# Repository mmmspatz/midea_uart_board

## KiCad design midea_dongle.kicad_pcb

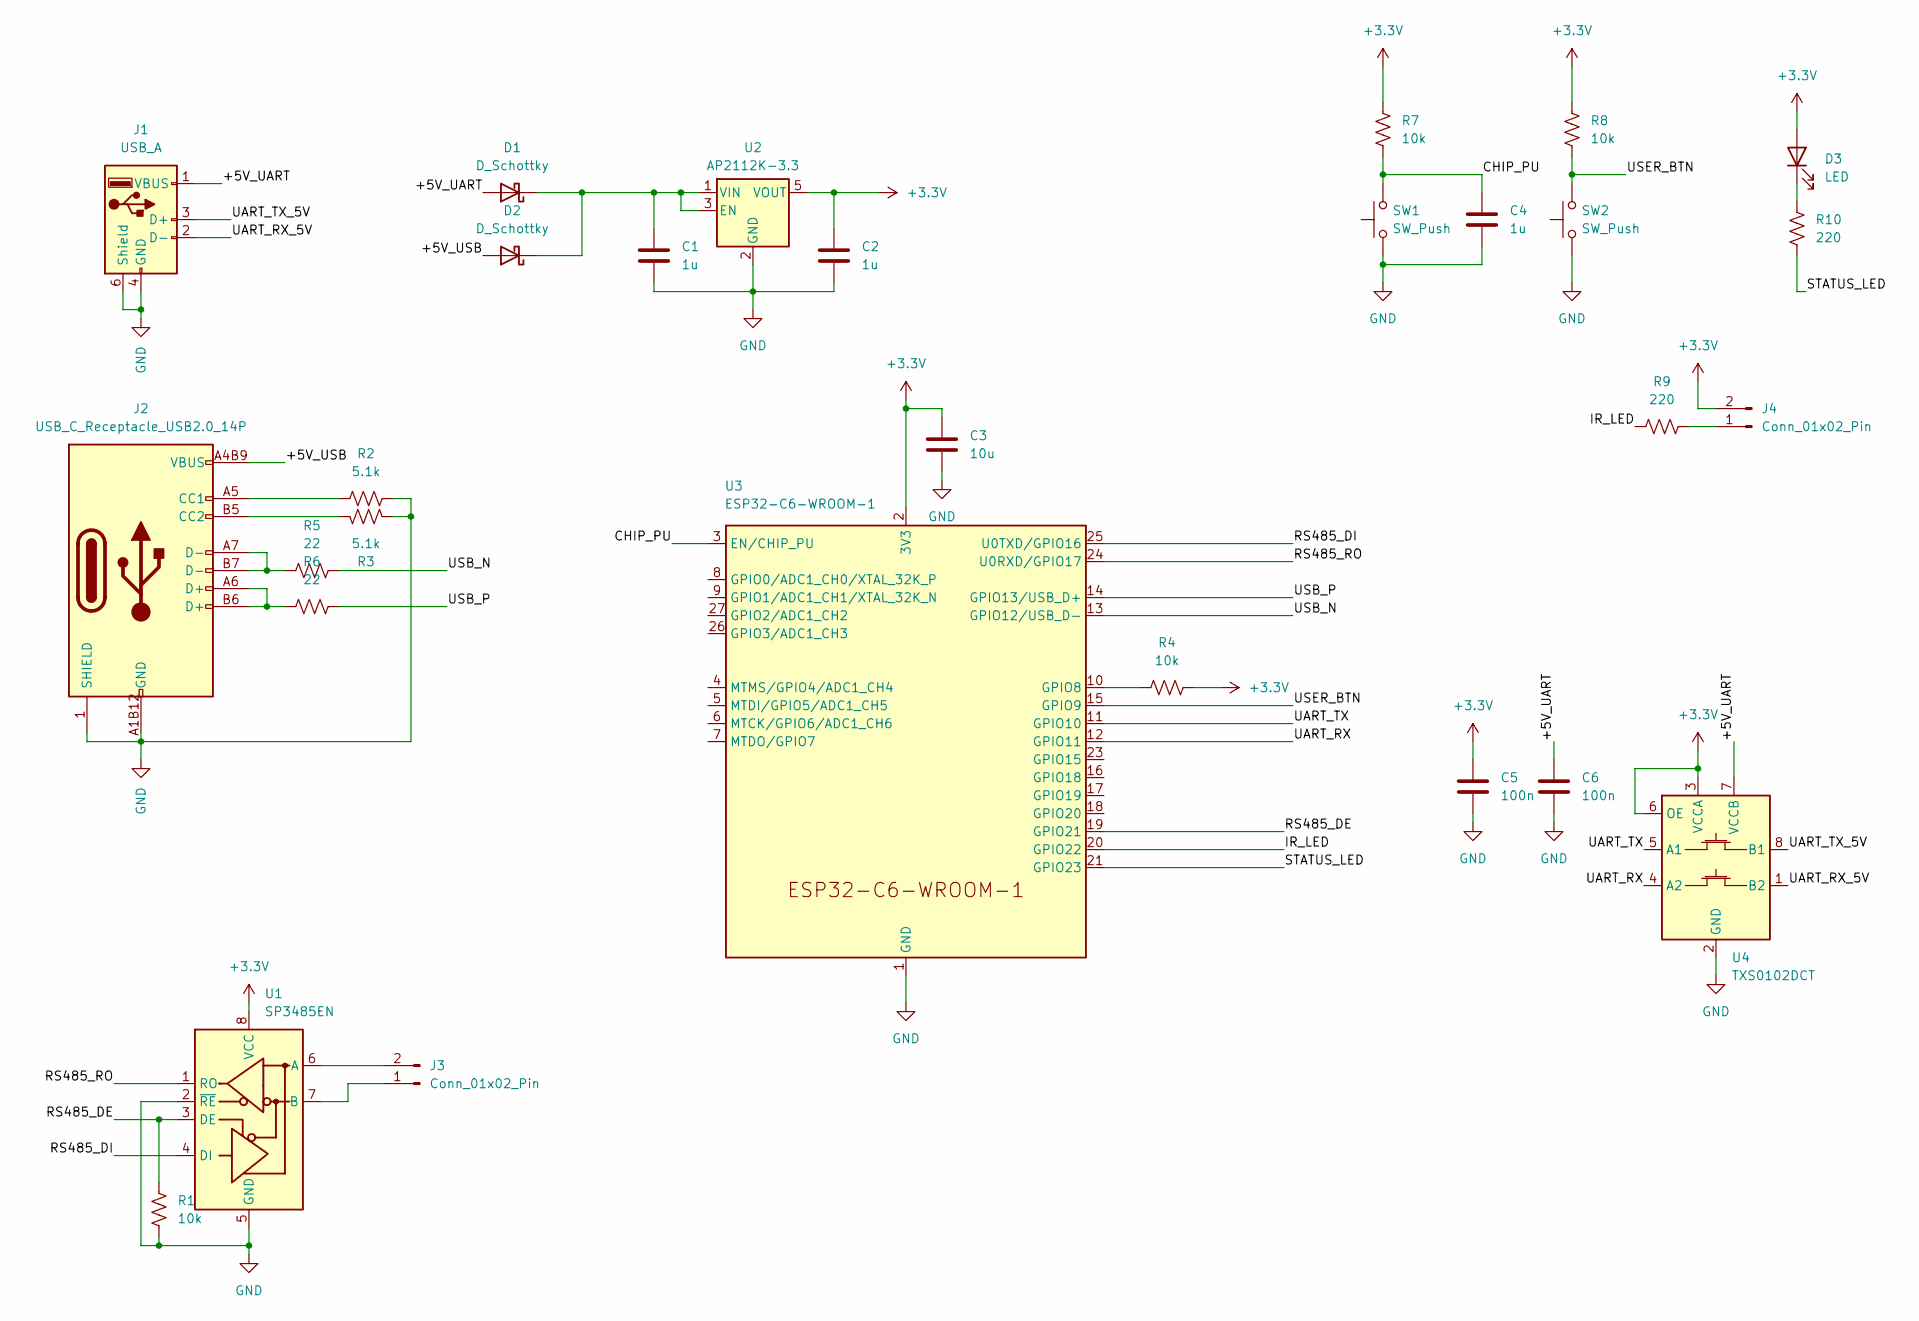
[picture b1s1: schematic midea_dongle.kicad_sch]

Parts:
C1, C2, C4: 1u; C_0402_1005Metric
C3: 10u; C_0603_1608Metric
C5, C6: 100n; C_0402_1005Metric
D1, D2: D_Schottky; D_SOD-123; LCSC C8598
D3: LED; LED_0603_1608Metric
J1: USB_A; USB-A-TH_U-G-04WD-W-01; LCSC C98125
J2: USB_C_Receptacle_USB2.0_14P; USB-C_SMD-TYPE-C-31-M-12_1; LCSC C165948
J3, J4: Conn_01x02_Pin; SMD_SOLPAD_1x02_p2.54mm
R1, R4, R7, R8: 10k; R_0402_1005Metric; LCSC C25744
R2, R3: 5.1k; R_0402_1005Metric
R5, R6: 22; R_0402_1005Metric
R9, R10: 220; R_0402_1005Metric
SW1, SW2: SW_Push; SW-SMD_L3.9-W3.0-P4.45
U1: SP3485EN; SOIC-8_3.9x4.9mm_P1.27mm
U2: AP2112K-3.3; SOT-23-5; LCSC C51118
U3: ESP32-C6-WROOM-1; LCSC C5366877
U4: TXS0102DCT; SSOP-8_2.95x2.8mm_P0.65mm

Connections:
+3.3V: C2.1, C3.1, C5.1, D3.2 (A), J4.2, R4.2, R7.2, R8.2, U1.8 (VCC), U2.5 (VOUT), U3.2 (3V3), U4.3 (VCCA), U4.6 (OE)
/+5V_UART: C6.1, D1.2 (A), J1.1 (VBUS), U4.7 (VCCB)
/+5V_USB: D2.2 (A), J2.A4B9 (VBUS), J2.B4A9 (VBUS)
/CHIP_PU: C4.1, R7.1, SW1.2, U3.3 (EN/CHIP_PU)
/IR_LED: R9.2, U3.20 (GPIO22)
/RS485_DE: R1.1, U1.3 (DE), U3.19 (GPIO21)
/RS485_DI: U1.4 (DI), U3.25 (U0TXD/GPIO16)
/RS485_RO: U1.1 (RO), U3.24 (U0RXD/GPIO17)
/STATUS_LED: R10.1, U3.21 (GPIO23)
/UART_RX: U3.12 (GPIO11), U4.4 (A2)
/UART_RX_5V: J1.2 (D-), U4.1 (B2)
/UART_TX: U3.11 (GPIO10), U4.5 (A1)
/UART_TX_5V: J1.3 (D+), U4.8 (B1)
/USB_N: R5.2, U3.13 (GPIO12/USB_D-)
/USB_P: R6.2, U3.14 (GPIO13/USB_D+)
/USER_BTN: R8.1, SW2.2, U3.15 (GPIO9)
GND: C1.2, C2.2, C3.2, C4.2, C5.2, C6.2, J1.4 (GND), J1.5 (Shield), J1.6 (Shield), J2.1 (SHIELD), J2.2 (SHIELD), J2.3 (SHIELD), J2.4 (SHIELD), J2.A1B12 (GND), J2.B1A12 (GND), R1.2, R2.2, R3.2, SW1.1, SW2.1, U1.2 (~RE), U1.5 (GND), U2.2 (GND), U3.1 (GND), U3.28 (GND), U3.29 (GND), U4.2 (GND)
unnamed: C1.1, D1.1 (K), D2.1 (K), U2.1 (VIN), U2.3 (EN)
unnamed: D3.1 (K), R10.2
unnamed: J2.A5 (CC1), R2.1
unnamed: J2.B5 (CC2), R3.1
unnamed: J2.A6 (D+), J2.B6 (D+), R6.1
unnamed: J2.A7 (D-), J2.B7 (D-), R5.1
unnamed: J3.1, U1.7 (B)
unnamed: J3.2, U1.6 (A)
unnamed: J4.1, R9.1
unnamed: R4.1, U3.10 (GPIO8)

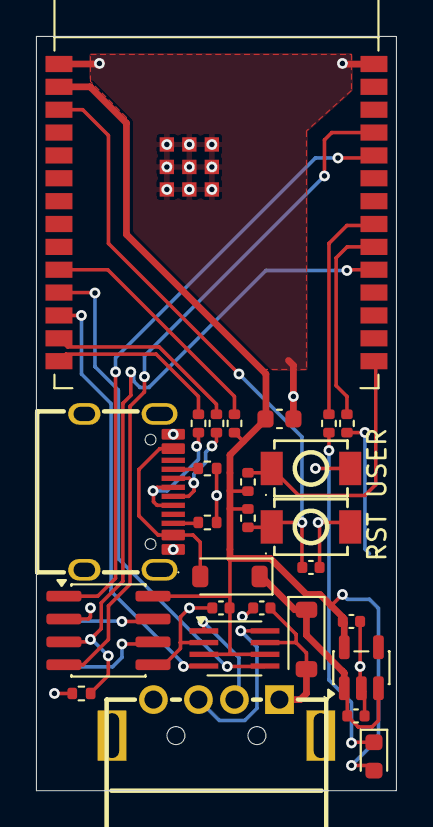
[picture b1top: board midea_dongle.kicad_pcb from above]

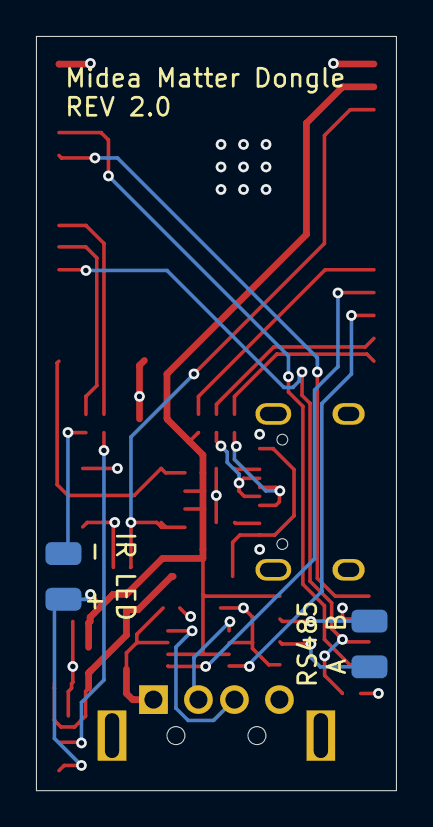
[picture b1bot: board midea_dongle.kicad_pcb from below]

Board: 4 copper layers, 20.0 x 41.9 mm, 29 parts (2 on the bottom side), 27 nets.

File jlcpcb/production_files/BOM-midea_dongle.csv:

Comment,Designator,Footprint,LCSC,Quantity
100n,"C5,C6",C_0402_1005Metric,C1525,2
10k,"R1,R4,R7,R8",R_0402_1005Metric,C25744,4
10u,C3,C_0603_1608Metric,C19702,1
1u,"C1,C2,C4",C_0402_1005Metric,C52923,3
22,"R5,R6",R_0402_1005Metric,C25092,2
220,"R10,R9",R_0402_1005Metric,C25091,2
5.1k,"R2,R3",R_0402_1005Metric,C25905,2
AP2112K-3.3,U2,SOT-23-5,C51118,1
D_Schottky,"D1,D2",D_SOD-123,C8598,2
ESP32-C6-WROOM-1,U3,ESP32-C6-WROOM-1,C5366877,1
LED,D3,LED_0603_1608Metric,C2286,1
SP3485EN,U1,SOIC-8_3.9x4.9mm_P1.27mm,C8963,1
SW_Push,"SW1,SW2",SW-SMD_L3.9-W3.0-P4.45,C720477,2
TXS0102DCT,U4,SSOP-8_2.95x2.8mm_P0.65mm,C324082,1
USB_A,J1,USB-A-TH_U-G-04WD-W-01,C98125,1
USB_C_Receptacle_USB2.0_14P,J2,USB-C_SMD-TYPE-C-31-M-12_1,C165948,1
